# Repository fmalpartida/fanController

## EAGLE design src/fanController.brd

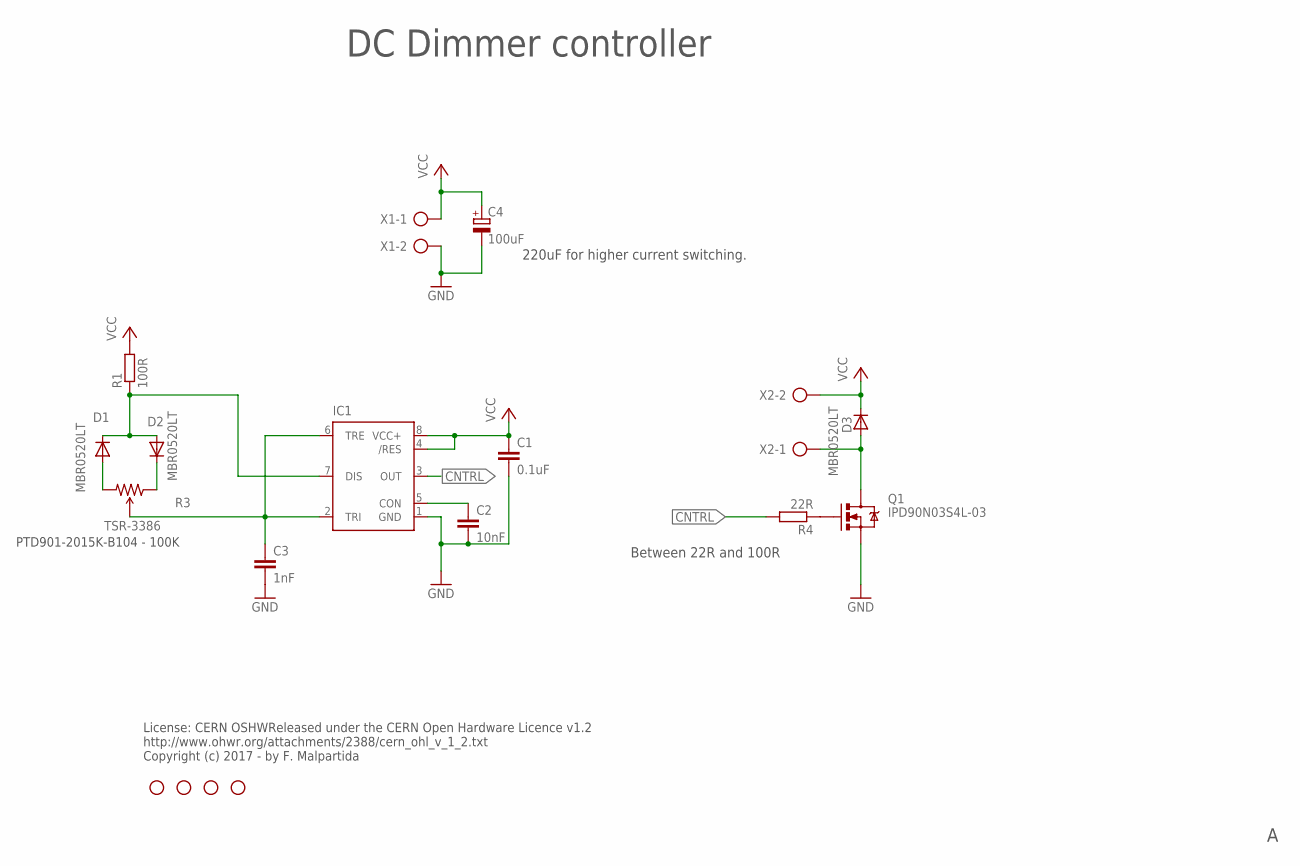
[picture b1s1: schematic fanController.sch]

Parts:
C1: 0.1uF; C0805
C2: 10nF; C0805
C3: 1nF; C0805
C4: 100uF; PANASONIC_D
D1, D2, D3: MBR0520LT; SOD123
IC1: NE555D; SO08
Q1: IPD90N03S4L-03; DPAK
R1: 100R; M0805
R3: TSR-3386; 3386U
R4: 22R; M0805
STANDOFF1, STANDOFF2, STANDOFF3, STANDOFF4: STAND-OFFTIGHT; STAND-OFF-TIGHT
X1, X2: AK500/2

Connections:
CNTRL: IC1.3 (OUT), R4.2
GND: C1.2, C2.2, C3.2, C4.-, IC1.1 (GND), Q1.3 (S), X1.2
unnamed: C2.1, IC1.5 (CON)
unnamed: D1.A, R3.3 (CW)
unnamed: Q1.1 (G), R4.1
unnamed: C3.1, IC1.2 (TRI), IC1.6 (TRE), R3.2 (WIPER)
unnamed: D1.C, D2.A, IC1.7 (DIS), R1.1
unnamed: D2.C, R3.1 (CCW)
unnamed: D3.A, Q1.4 (D), X2.1
VCC: C1.1, C4.+, D3.C, IC1.4 (/RES), IC1.8 (VCC+), R1.2, X1.1, X2.2

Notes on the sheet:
PTD901-2015K-B104 - 100K
DC Dimmer controller
License: CERN OSHWReleased under the CERN Open Hardware Licence v1.2 http://www.ohwr.org/attachments/2388/cern_ohl_v_1_2.txt Copyright (c) 2017 - by F. Malpartida
220uF for higher current switching.
Between 22R and 100R

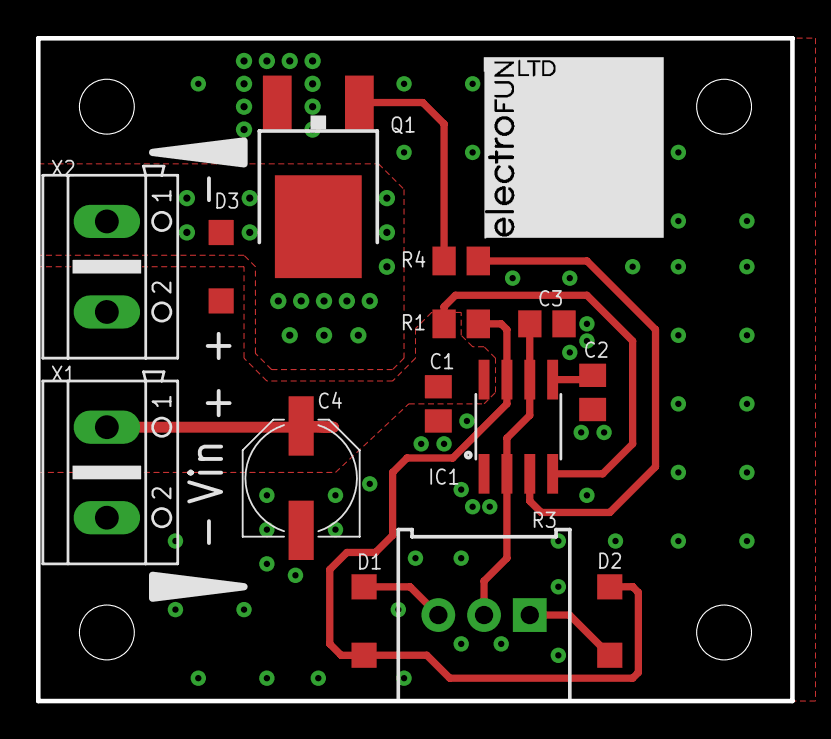
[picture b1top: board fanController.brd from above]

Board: 2 copper layers, 41.9 x 36.8 mm, 20 parts (1 on the bottom side), 10 nets.

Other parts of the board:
U$1: BOARD_REF
U$2: ELECTROFUN_10X10

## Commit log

2016-05-21 Simple PWM fan controller up to 4A fan loads.
2016-05-21 Updated fan controller.
2017-03-12 Updated final version.
2017-03-19 Reworked controller for different configuration.
2017-03-19 Updated documentation and layout.
2017-03-19 Updated project file.
2017-03-19 Updated Rev B for production.
2017-03-19 Update 10nF cap to 1nF
2017-03-26 Minos adjustments to schematic.
2017-04-23 Added gerber files for ordering.
2017-05-01 Schematic touchups for final release after testing. Added alternative values to the schematics.

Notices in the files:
parts and their libraries:
SparkFun-AnalogIC: Licensing:Creative Commons ShareAlike 4.0 International - https://creativecommons.org/licenses/by-sa/4.0
